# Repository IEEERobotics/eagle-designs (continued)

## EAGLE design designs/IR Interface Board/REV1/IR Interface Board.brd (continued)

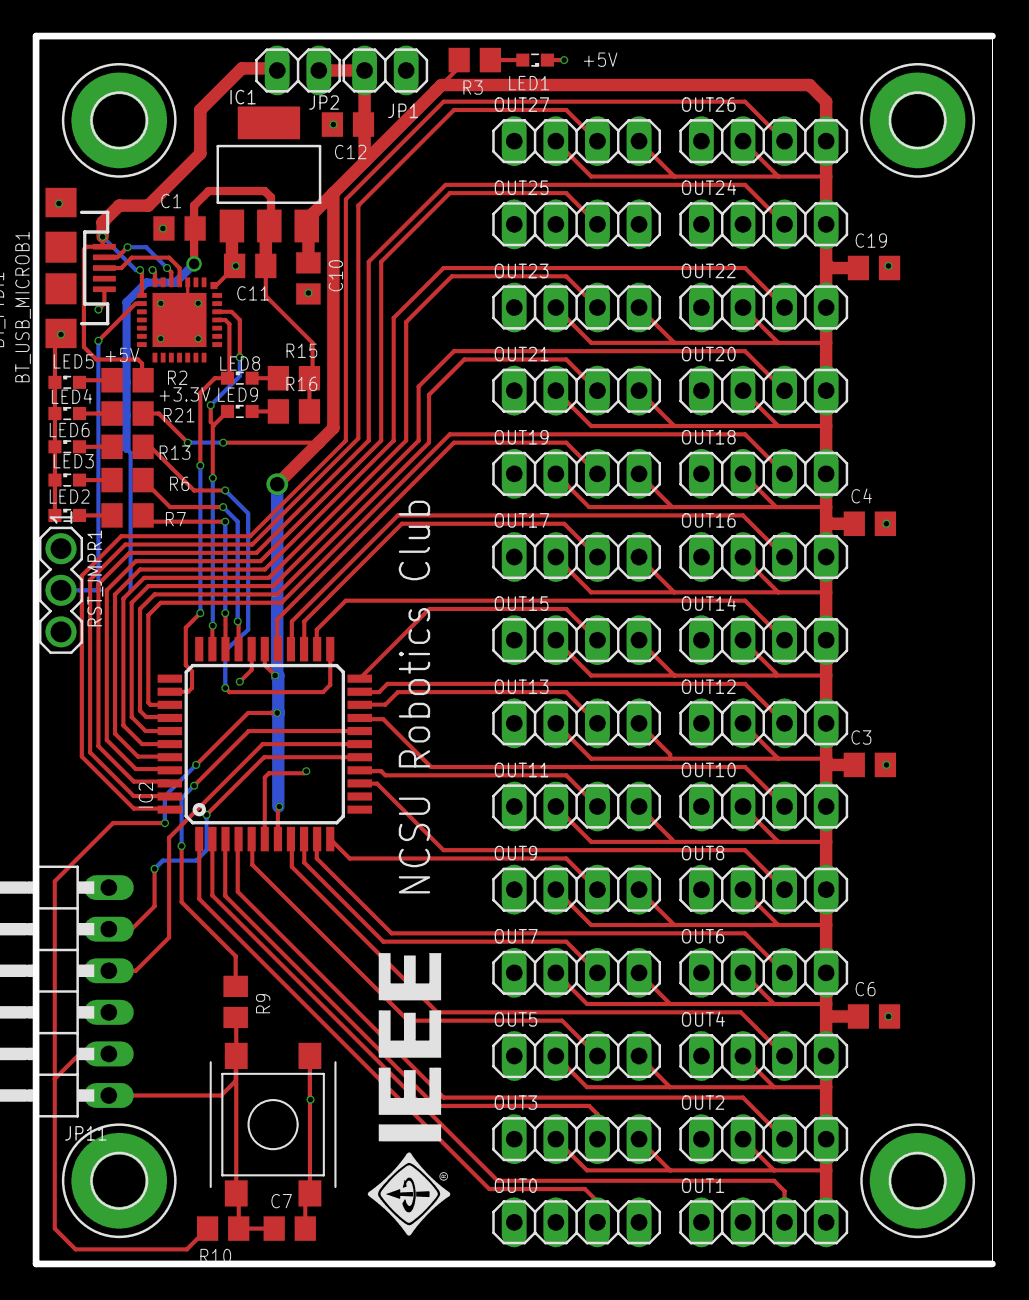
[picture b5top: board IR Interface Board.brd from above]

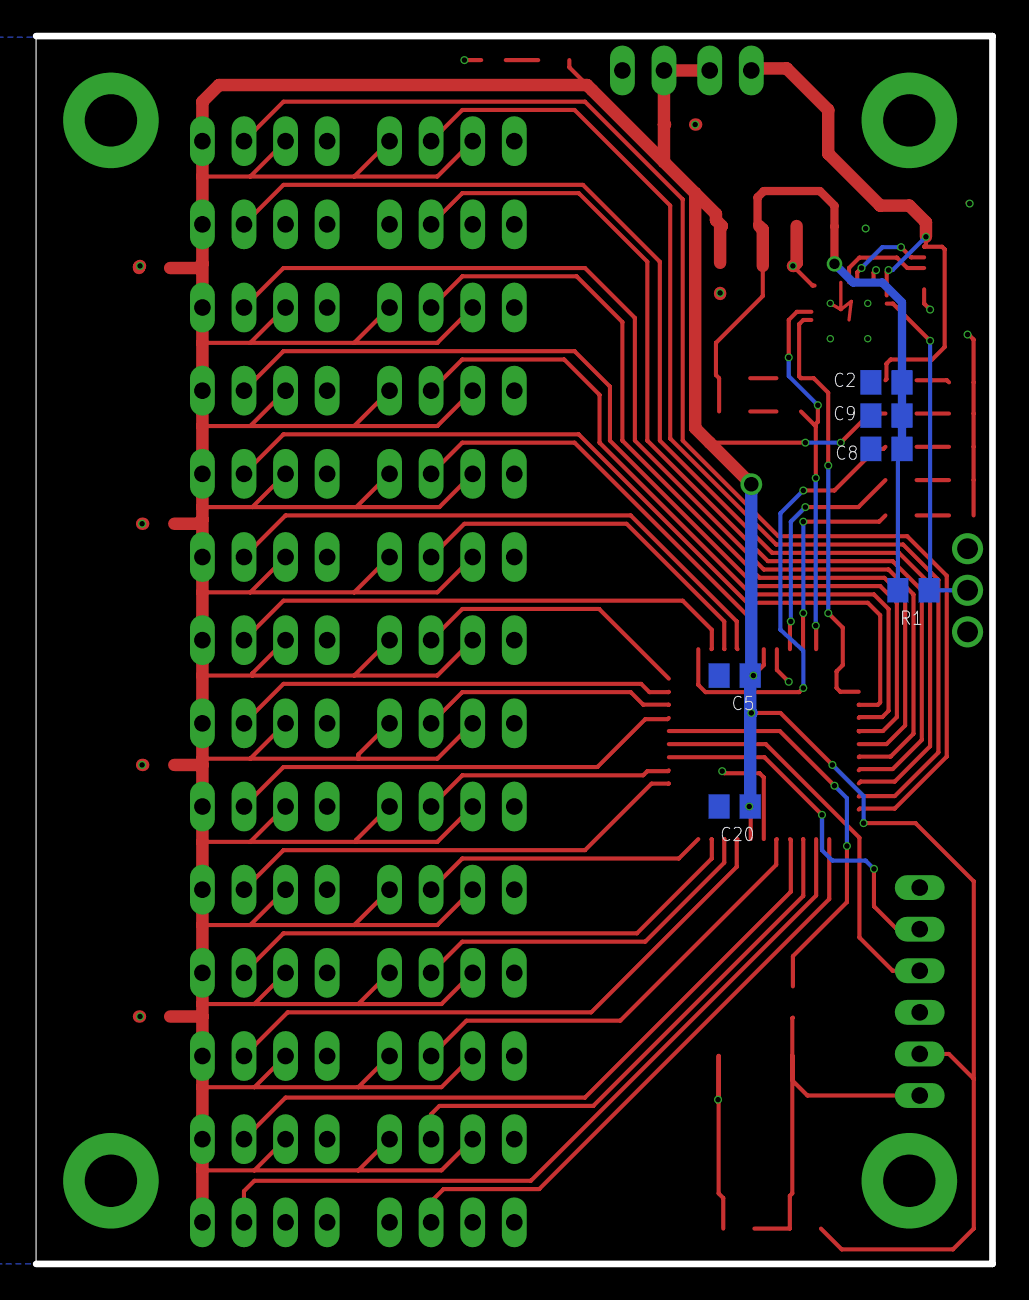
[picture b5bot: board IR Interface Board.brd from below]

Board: 2 copper layers, 58.4 x 75.0 mm, 75 parts (6 on the bottom side), 52 nets.
